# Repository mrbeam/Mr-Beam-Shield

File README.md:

# README #

### Mr Beam Shield ###

* The Mr Beam Shield is a grbl compatible Arduino Shield which combines 3 stepper motor driver sockets (pololu/stepstick compatible) with a laser diode driver 
* Version 1.1
* 

### How do I get set up? ###

* See manual.pdf in this repository for a detailed description of the shield.

### Who do I talk to? ###

* The Mr Beam Shield was developed for the Mr Beam Laser Cutter Kit, published on Kickstarter May 2014
* get in touch for any purpose: support@mr-beam.org

### LICENSE ###
This work is licensed under the Creative Commons Attribution-NonCommercial-ShareAlike 4.0 International License. 
To view a copy of this license, visit http://creativecommons.org/licenses/by-nc-sa/4.0/.

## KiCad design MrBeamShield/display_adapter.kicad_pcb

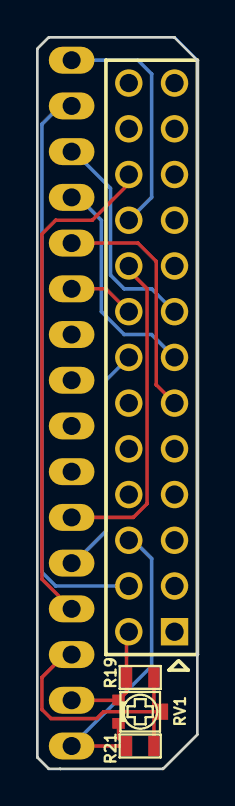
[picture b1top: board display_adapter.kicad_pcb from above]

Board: 2 copper layers, 8.9 x 40.6 mm, 6 parts (0 on the bottom side), 12 nets.

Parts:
P12: CONN_RPi; pin_array_13x2
P13: CONN_1_8; connector_1x8
P17: CONN_9_16; connector_1x8
R19, R21: R; r_0603
RV1: 10K; trim_murata_pvz2a

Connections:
unnamed: P12.6, P13.1, R21.2, RV1.3
unnamed: P13.3, R19.2, R21.1, RV1.2
unnamed: P12.22, P13.4
unnamed: P12.20, P17.8
unnamed: P12.18, P13.6
unnamed: P12.16, P17.3
unnamed: P12.15, P17.6
unnamed: P12.11, P17.4
unnamed: P12.13, P17.5
unnamed: P12.2, P13.2, R19.1, RV1.1
unnamed: P12.4, P17.7
unnamed: P12.14, P13.5

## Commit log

2016-04-05 cleaned kicad project files
